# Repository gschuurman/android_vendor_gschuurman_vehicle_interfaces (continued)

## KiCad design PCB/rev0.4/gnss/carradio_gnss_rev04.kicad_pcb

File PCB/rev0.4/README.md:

# PCB rev 0.4: main board plus three plug-in modules

Rev 0.4 splits rev 0.3 into four boards so each one fits the JLCPCB 100 x 100 mm price tier, and spreads
the parts out for hand soldering (at least 0.8 mm between courtyards on every board).

| Board | Folder | Size | Layers | Holds |
|---|---|---|---|---|
| Main | `main/` | 100 x 100 mm, four M3 holes 4.5 mm in from each corner | 4 | RP2350B, TPS55288 VIM3/screen supply, always-on buck, car inputs, GNSS 3.3 V LDO, hub 1, HDMI-to-FPC screen adapter, loom connectors |
| GNSS module | `gnss/` | 26.5 x 31.5 mm | 2 | u-blox NEO-M9N, U.FL antenna receptacle with active-antenna feed, USB series resistors |
| Audio module | `audio/` | 36.5 x 41 mm | 2 | 2x PCM5102A, 2 LDOs, output filters |
| USB module | `usb/` | 36 x 55 mm (USB-A shells stick out 0.55 mm on the right) | 2 | Hub 2, two phone ports (LMR33630 5V/3A, TPS2561 limits, ESD), RTL-SDR USB-A socket |

Each board has its own schematic, PCB, PDF, netlist and BOM. **Status 2026-10-02: the three modules are routed (DRC clean); the main board is placed with the HDMI and TPS55288 copper in place, and its signal routing is still in progress.** All four come from `gen4.py` (`python3 gen4.py main|gnss|audio|usb`).

## Changes since the first rev 0.4 draft

- The NEO-M9N moved from the main board onto its own swappable GNSS module (Glenn, 2026-10-02). The antenna plugs into a
  U.FL receptacle J11 (Hirose U.FL-R-SMT-1, LCSC C88374); use a U.FL-to-SMA bulkhead pigtail to reach the car antenna.
- The GNSS module gets both USB and UART:
  - USB goes to hub 1 port 3 (it shows up as a CDC-ACM serial port, `/dev/ttyACM*`).
  - UART TX goes to the VIM3 UART_C RX (header pin 15) through R100 and to the RP2350B.
  - UART RX is driven by the VIM3 UART_C TX (header pin 16, through R101) or by the RP2350B, picked with
    solder jumper JP2: 1-2 VIM3 (default, bridged), 2-3 MCU. Cut the 1-2 trace and bridge 2-3 to hand GNSS
    config to the MCU.
- The RTL-SDR socket moved from hub 1 to hub 2 on the USB module, so USB module header pins 9 and 11 are now unused.
- J18 (VIM3 power, JST-XH) and J5 (power-on lead) now sit right below the VIM3 40-pin header at the top left.
- Parts now sit under the modules (MCU, hub 1, GNSS LDO, J21/J10), which freed space for wider spacing.
- Hub 1 (U13) now runs from the always-on +5V_AON instead of +5V_SYS, with a 10k pull-up (R104) on its reset pin.
  A blank RP2350B therefore enumerates as soon as 12V is applied, so the first flash works over USB (Glenn, 2026-10-02).

## How the modules stack

- The main board carries female sockets (8.5 mm tall): J27 (2x8) for GNSS, J23 (2x10) for audio, J25 (2x10) for USB.
- Each module has a male header (J28, J24, J26) **soldered on its underside**, pins pointing down. In KiCad the
  header footprint sits on the bottom layer, so pin n of the header lands on pin n of the socket.
- Each module PCB sits about 11 mm above the main board. Everything under a module is a low SMD part.
- One M2.5 standoff (11 mm) per module, at the far side from its header. Main-board positions:

| Module | Covers main board (x, y in mm) | Standoff hole on main |
|---|---|---|
| GNSS | 0-26.5, 19-50.5 | (3.2, 34.3) |
| Audio (turned 90°) | 27-63.5, 13-54 | (31.0, 16.5) |
| USB | 64-100, 32.5-87.5 (USB-A sockets on the right edge) | (67.8, 83.7) |

- J21 and J10 (main board headers) are under the USB module: unplug the module to reach them.
- SW1, SW2, JP1, Q2 and Q3 sit in the open strip between the audio and USB modules.

## Header pin maps

GNSS (J27 on main, J28 on module):

| Pin | Net | Pin | Net |
|---|---|---|---|
| 1 | +3V3_GNSS (switched by the MCU) | 2 | +3V3_GNSS |
| 3 | GND | 4 | +3V3_MCU (NEO V_BCKP, keeps hot start) |
| 5 | not connected | 6 | GND |
| 7 | GNSS_USB_DP | 8 | GNSS_TXD |
| 9 | GNSS_USB_DM | 10 | GNSS_RXD |
| 11 | GND | 12 | GND |
| 13 | GNSS_RST | 14 | GNSS_PPS |
| 15 | GNSS_SAFEBOOT | 16 | GND |

Audio (J23 on main, J24 on module):

| Pin | Net | Pin | Net |
|---|---|---|---|
| 1 | VIM3_5V | 2 | VIM3_5V |
| 3 | GND | 4 | GND |
| 5 | I2S_BCLK | 6 | GND |
| 7 | I2S_LRCK | 8 | VIM3_I2S_MCLK (spare) |
| 9 | I2S_DOUT0 | 10 | I2S_DOUT1 |
| 11 | VIM3_I2S_DOUT2 (spare) | 12 | DAC_XSMT |
| 13 | LUX_SCL (spare) | 14 | LUX_SDA (spare) |
| 15 | GND | 16 | GND |
| 17 | LINE_FL | 18 | LINE_FR |
| 19 | LINE_RL | 20 | LINE_RR |

USB (J25 on main, J26 on module):

| Pin | Net | Pin | Net |
|---|---|---|---|
| 1 | VSYS_IN (12V, for the 5V/3A buck) | 2 | VSYS_IN |
| 3 | GND | 4 | GND |
| 5 | +5V_SYS | 6 | +5V_SYS |
| 7 | GND | 8 | GND |
| 9 | not connected (was SDR) | 10 | HUB2_UP_DP |
| 11 | not connected (was SDR) | 12 | HUB2_UP_DM |
| 13 | GND | 14 | GND |
| 15 | MCU_USBP_PG | 16 | VIM3_PWR_EN |
| 17 | MCU_USBP_FAULT2 | 18 | MCU_USBP_FAULT1 |
| 19 | not connected | 20 | GND |

## GNSS in Android: what "native" needs

Today the project's GNSS HAL (`usb_gnss_hal/`, AIDL IGnss) reads NMEA from a hard-coded `/dev/ttyAML6` at 9600 baud
and sends UBX config itself. Android has no stock NMEA/serial GNSS HAL (AOSP's default one is a mock), so a HAL
of our own stays in the picture either way. "Native" here means letting the Linux kernel own the device.

UART path (kernel GNSS subsystem, `/dev/gnss0`):
1. Kernel config (vim3 fragment): `CONFIG_GNSS_SERIAL=m` and `CONFIG_GNSS_UBX_SERIAL=m` (`CONFIG_GNSS=m` is already on).
2. Device tree: a child node under `&uart_C`:
   `gnss { compatible = "u-blox,neo-m8"; current-speed = <38400>; };`
   The ubx driver has no M9 entry, but the neo-m8 binding works the same for the M9N. The driver also
   handles the `vcc`/`v-bckp` supplies if they are described; here the MCU switches the supply, so they can be left out.
3. HAL: open `/dev/gnss0` instead of `/dev/ttyAML6`, plus ueventd and sepolicy rules for `/dev/gnss*`.
   This also removes the clash between the `ttyAML.*` gnss label and the serial console.
4. Baud: the NEO-M9N UART default is 38400 (from memory; check the M9N integration manual), while the HAL uses 9600.

USB path (kept for the existing HAL design):
1. The NEO-M9N enumerates as u-blox VID 0x1546, CDC-ACM; `cdc-acm.ko` is already loaded, so it appears as `/dev/ttyACM*`.
2. Add a ueventd rule and a udev-style stable symlink by VID (or have the HAL scan `/sys/class/tty/ttyACM*` for VID 1546),
   plus sepolicy for that device.

Both paths can run at the same time; NEO-M9N outputs the same NMEA on UART and USB.

## RP2350B GPIO map (rev 0.4)

Re-assigned on 2026-10-02 so each signal leaves the QFN on the side facing its destination, which makes routing
possible. This replaces the rev 0.3 map in DESIGN_rev03.md; the draft firmware's pin table needs the same update.
Expansion nets are named after their GPIO (EXP_GPn).

| GPIO | Net | Notes |
|---|---|---|
| GPIO0 | MCU_BL_EN |  |
| GPIO1 | MCU_BL_PWM |  |
| GPIO2 | MCU_HUB_RST |  |
| GPIO3 | MCU_GNSS_PPS |  |
| GPIO4 | MCU_GNSS_TX | UART1 TX to GNSS (via JP2 2-3) |
| GPIO5 | MCU_GNSS_RX | UART1 RX from GNSS |
| GPIO6 | MCU_SBC_SENSE |  |
| GPIO7 | MCU_GNSS_RST |  |
| GPIO8 | MCU_GNSS_SAFEBOOT |  |
| GPIO9 | MCU_GNSS_EN |  |
| GPIO10 | MCU_DAC_MUTE |  |
| GPIO11 | EXP_GP11 | expansion header J10/J21 |
| GPIO12 | EXP_GP12 | expansion header J10/J21 |
| GPIO13 | EXP_GP13 | expansion header J10/J21 |
| GPIO14 | MCU_PARK_IN |  |
| GPIO15 | MCU_PWR_KEY |  |
| GPIO16 | MCU_BTN_MUTE |  |
| GPIO17 | MCU_BTN_VOLUP |  |
| GPIO18 | MCU_BTN_SCREEN |  |
| GPIO19 | MCU_SERVICE |  |
| GPIO20 | MCU_AMP_EN |  |
| GPIO21 | MCU_LED |  |
| GPIO22 | MCU_BTN_VOLDN |  |
| GPIO23 | MCU_VIM3_PWR_EN |  |
| GPIO24 | EXP_GP24 | expansion header J10/J21 |
| GPIO25 | EXP_GP25 | expansion header J10/J21 |
| GPIO26 | EXP_GP26 | expansion header J10/J21 |
| GPIO27 | EXP_GP27 | expansion header J10/J21 |
| GPIO28 | EXP_GP28 | expansion header J10/J21 |
| GPIO29 | EXP_GP29 | expansion header J10/J21 |
| GPIO30 | LUX_SDA | I2C1 SDA (light sensor, TPS55288, audio module) |
| GPIO31 | LUX_SCL | I2C1 SCL |
| GPIO32 | EXP_GP32 | J10 pin 2 (K-line UART TX) |
| GPIO33 | EXP_GP33 | J10 pin 3 (K-line UART RX) |
| GPIO34 | EXP_GP34 | expansion header J10/J21 |
| GPIO35 | MCU_REV_IN |  |
| GPIO36 | MCU_USBP_PG |  |
| GPIO37 | MCU_ILLUM_IN |  |
| GPIO38 | MCU_USBP_FAULT2 |  |
| GPIO39 | MCU_USBP_FAULT1 |  |
| GPIO40 | MCU_VBAT_ADC | ADC0 battery voltage |
| GPIO41 | MCU_5VSYS_ADC | ADC1 5V rail |
| GPIO42 | MCU_TEMP_ADC | ADC2 board temperature |
| GPIO43 | MCU_ACC_IN |  |
| GPIO44 | unused |  |
| GPIO45 | unused |  |
| GPIO46 | unused |  |
| GPIO47 | unused |  |

## Flashing the RP2350B

- Over USB: hold SW1 (BOOTSEL), tap SW2 (RESET); the chip shows up as a USB drive `RP2350` on whatever hosts hub 1.
  A blank flash starts the bootloader by itself. The host is normally the VIM3 (`picotool` from a root adb shell), or a PC
  on a breakout cable to J2 pins 2-5 (5V, D-, D+, GND) with the board off the VIM3 and 12V applied.
- Over SWD: J22 (SWCLK, GND, SWDIO, RUN) with a Raspberry Pi Debug Probe or a Pico running `debugprobe`, for recovery and debugging.
- Firmware should hold hub 1 in reset (MCU_HUB_RST low) while the VIM3 is off, to save parked current and keep the hub's
  D+ pull-up off the unpowered VIM3.

## Hand soldering

Most parts are 0805 or larger SOIC/SOT parts. These need hot air or a hotplate with paste, not an iron:
- RP2350B (QFN-80, 0.4 mm pitch), TPS55288 (VQFN-HR), NEO-M9N (LGA), Q11/Q12 and U16 (VSON/QFN power packages).
- J13 (HDMI) and J14 (0.5 mm FPC) have fine-pitch SMD pins; drag soldering with flux works, but check for bridges.
Ordering the bare boards with only those parts assembled by JLCPCB is an option.

## Main board notes

- HDMI J13 (top edge) to the screen FPC J14 (right edge) is routed on F.Cu over the In1 ground plane with no vias.
  Each pair is matched to 0.001 mm. An In1 rule area keeps vias out from under the runs.
- J14 keeps pin 1 on the right when seen from the top with the ribbon leaving the board edge.
- The TPS55288 power stage (U12, Q11/Q12, L3, gate resistors, snubber, net ties) is carried over from rev 0.3
  with its copper. +5V_SYS reaches J18 through an In2 copper strip.

## GNSS module notes

- The U.FL receptacle J11 sits at the module's left side, about 3 mm from the main board's left edge, so a pigtail can leave sideways.
- The RF line from J11 to the NEO is a 1.0 mm trace over solid B.Cu ground with stitching vias; B.Cu under it has
  no tracks. Check the 50 Ω width with the JLCPCB impedance calculator for the 2-layer 1.6 mm stack before ordering.
- L2 (active-antenna feed choke) is 0402, the one tiny passive left.

## Open items before ordering

- LCSC numbers for the 2x8 socket J27 and 2x8 header J28 (any 2.54 mm, 8.5 mm female socket fits).
- J23/J25 socket part C30867 was out of stock at LCSC on 2026-10-01; any 2x10 2.54 mm 8.5 mm female socket fits.
- The USB module's LMR33630 buck layout is auto-routed with widened copper; not yet checked against TI's layout guide.
- Bench test the TPS55288 loop (unchanged from rev 0.3).

## Layout scripts

`layout/` holds the scripts that made the boards (run in the `kicad/kicad:10.0` Docker image). See rev 0.3's
`layout/README.md` for the shared tools.

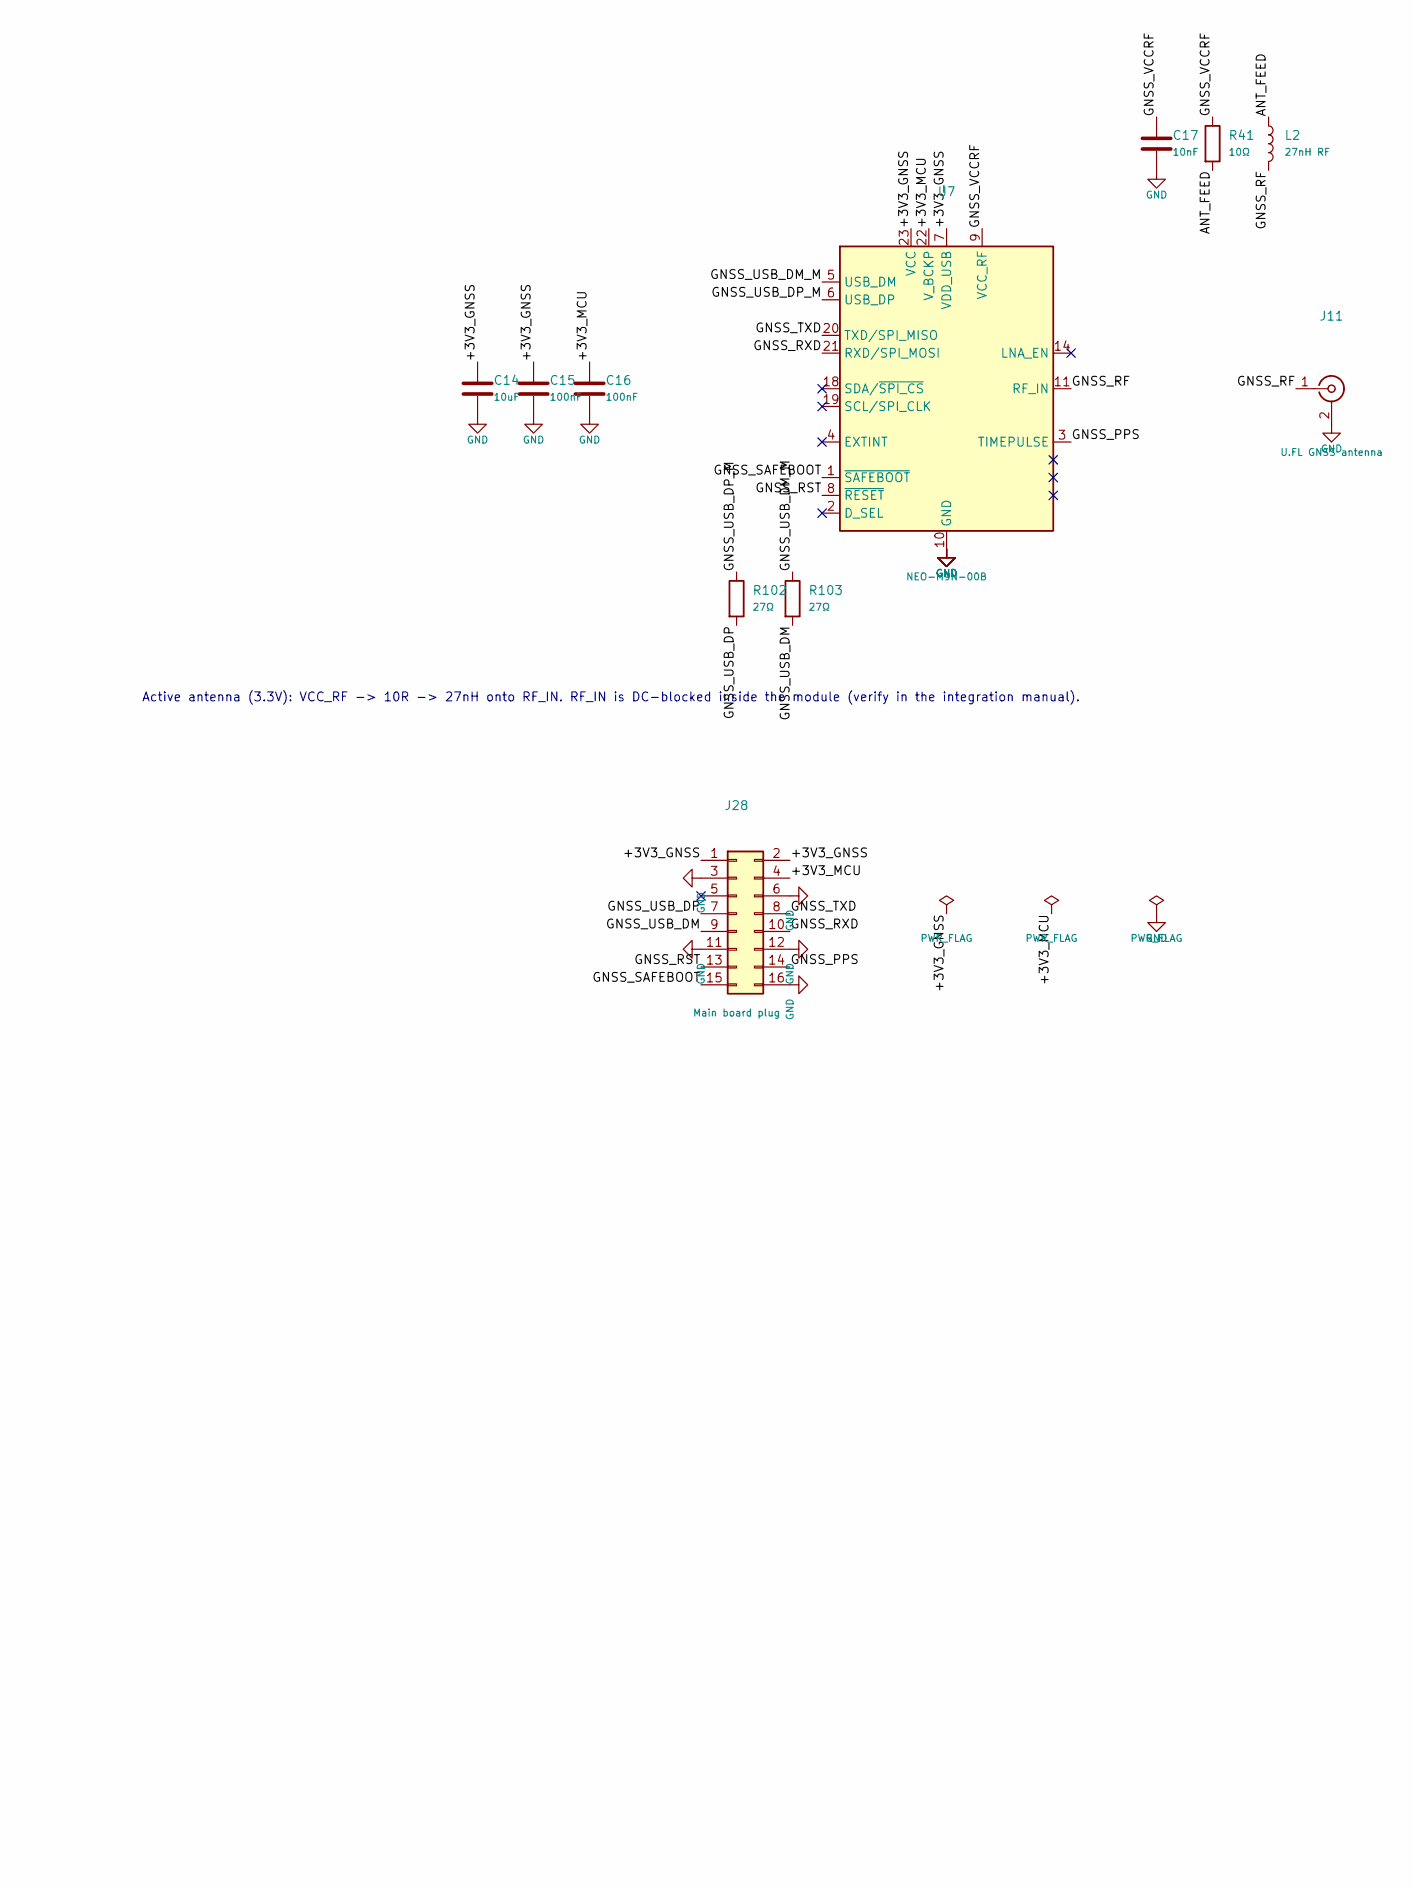
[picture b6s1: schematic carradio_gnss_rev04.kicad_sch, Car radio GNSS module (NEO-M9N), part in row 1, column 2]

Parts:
C14: 10uF; C_0805_2012Metric; MPN 0805 10uF 25V X5R; LCSC C15850
C15, C16: 100nF; C_0603_1608Metric; MPN 0603 100nF 50V X7R; LCSC C14663
C17: 10nF; C_0603_1608Metric; MPN 0603 10nF 50V X7R (Samsung CL10B103KB8N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; LCSC C1589
J11: U.FL GNSS antenna; U.FL_Hirose_U.FL-R-SMT-1_Vertical; MPN Hirose U.FL-R-SMT-1(80) U.FL receptacle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; LCSC C88374
J28: Main board plug; PinHeader_2x08_P2.54mm_Vertical; MPN 2x8 2.54mm male pin header
L2: 27nH RF; L_0402_1005Metric; MPN Murata LQG15HS27NJ02D; LCSC C12669
R41: 10Ω; R_0603_1608Metric; MPN 0603 10 1%; LCSC C22859
R102, R103: 27Ω; R_0603_1608Metric; MPN 0603 27 1%
U7: NEO-M9N-00B; ublox_NEO; MPN u-blox NEO-M9N-00B; LCSC C5119087

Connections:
/+3V3_GNSS: C14.1, C15.1, J28.1, J28.2, U7.7 (VDD_USB), U7.23 (VCC)
/+3V3_MCU: C16.1, J28.4, U7.22 (V_BCKP)
/ANT_FEED: L2.1, R41.2
/GNSS_PPS: J28.14, U7.3 (TIMEPULSE)
/GNSS_RF: J11.1 (In), L2.2, U7.11 (RF_IN)
/GNSS_RST: J28.13, U7.8 (~RESET)
/GNSS_RXD: J28.10, U7.21 (RXD/SPI_MOSI)
/GNSS_SAFEBOOT: J28.15, U7.1 (~SAFEBOOT)
/GNSS_TXD: J28.8, U7.20 (TXD/SPI_MISO)
/GNSS_USB_DM: J28.9, R103.2
/GNSS_USB_DM_M: R103.1, U7.5 (USB_DM)
/GNSS_USB_DP: J28.7, R102.2
/GNSS_USB_DP_M: R102.1, U7.6 (USB_DP)
/GNSS_VCCRF: C17.1, R41.1, U7.9 (VCC_RF)
GND: C14.2, C15.2, C16.2, C17.2, J11.2 (Ext), J28.3, J28.6, J28.11, J28.12, J28.16, U7.10 (GND), U7.12 (GND), U7.13 (GND), U7.24 (GND); also elsewhere on the board

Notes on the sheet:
Active antenna (3.3V): VCC_RF -> 10R -> 27nH onto RF_IN. RF_IN is DC-blocked inside the module (verify in the integration manual).
Car radio GNSS module rev 0.4 - NEO-M9N with SMA antenna jack; plugs onto the peripheral board (J28 -> J27). Generated by gen4.py gnss.

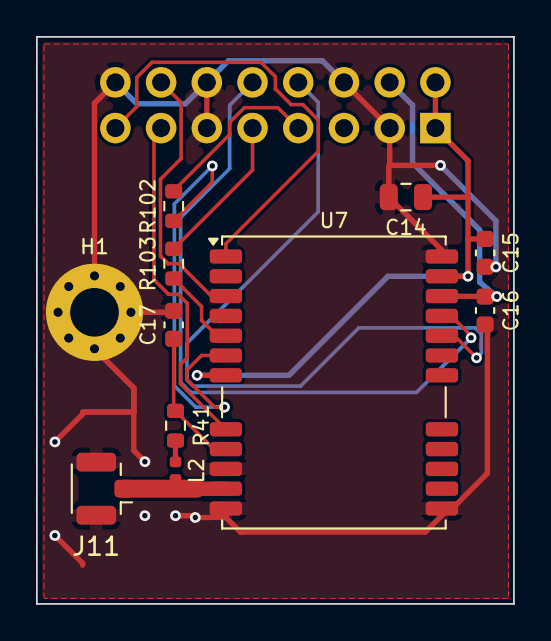
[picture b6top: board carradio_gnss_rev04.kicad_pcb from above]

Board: 2 copper layers, 26.5 x 31.5 mm, 12 parts (1 on the bottom side), 15 nets.

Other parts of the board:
H1: M2.5 standoff; MountingHole_2.7mm_M2.5_Pad_Via

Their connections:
GND: H1.1; also elsewhere on the board

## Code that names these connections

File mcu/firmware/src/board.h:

// RP2350B pin map for the car radio peripheral board, rev 0.6.
//
// Taken from the rev 0.6 main-board netlist (PCB/rev0.6/main/carradio_peripheral_rev06.net,
// U20). The comment after each pin names the net and the parts that set its idle level.
#pragma once

#define BOARD_REV 6

// ---- Car inputs: EL817 opto, emitter to the pin, 4.7k pull-down. High = 12V present. ----
#define PIN_ACC_IN        43  // /MCU_ACC_IN    U2, R4 (ISO A7, via F2)
#define PIN_ILLUM_IN      37  // /MCU_ILLUM_IN  U3, R6 (ISO A6)
#define PIN_REV_IN        35  // /MCU_REV_IN    U4, R30 (ISO A1)
#define PIN_PARK_IN       14  // /MCU_PARK_IN   U5, R32 (ISO A2, switch to ground; open = released)

// ---- Other inputs ----
#define PIN_SBC_SENSE      6  // /MCU_SBC_SENSE  VIM3 3.3V via R7 1k, R8 4.7k pull-down. High = VIM3 on
#define PIN_SERVICE       19  // /MCU_SERVICE    JP1 to 3.3V, R9 4.7k pull-down. High = service mode
#define PIN_USBP_PG       36  // /MCU_USBP_PG    USB module LMR33630 PG, R89 10k pull-up. High = good
#define PIN_USBP_FAULT1   39  // /MCU_USBP_FAULT1 TPS2561 FAULT, R87 10k pull-up. Low = over-current
#define PIN_USBP_FAULT2   38  // /MCU_USBP_FAULT2 R88 10k pull-up. Low = over-current
#define PIN_GNSS_PPS       3  // /MCU_GNSS_PPS   via R40 1k, R94 4.7k pull-down

// ---- Display buttons J12: switch to GND, 10k pull-up, 1k + 100nF RC. Low = pressed ----
#define PIN_BTN_SCREEN    18  // /MCU_BTN_SCREEN J12.1
#define PIN_BTN_VOLUP     17  // /MCU_BTN_VOLUP  J12.2
#define PIN_BTN_VOLDN     22  // /MCU_BTN_VOLDN  J12.3
#define PIN_BTN_MUTE      16  // /MCU_BTN_MUTE   J12.4

// ---- Outputs ----
#define PIN_VIM3_PWR_EN   23  // /MCU_VIM3_PWR_EN R73 1k -> TPS55288 EN + USB module enable; R72 100k pull-down
#define PIN_PWR_KEY       15  // /MCU_PWR_KEY    R12 390R -> AQY210S U22 LED. High = VIM3 power key pressed
#define PIN_AMP_EN        20  // /MCU_AMP_EN     R16 -> Q3 2N7002 -> amp remote (ISO A3). R15 pull-down
#define PIN_BL_EN          0  // /MCU_BL_EN      R23 -> panel FPC pin 37. R96 100k pull-down
#define PIN_BL_PWM         1  // /MCU_BL_PWM     R24 -> panel FPC pin 36. Inverted: low = brightest
#define PIN_DAC_MUTE      10  // /MCU_DAC_MUTE   R46 1k -> DAC XSMT, R47 10k pull-down. High = play
#define PIN_HUB_RST        2  // /MCU_HUB_RST    R90 1k -> CH334R RESET#, R104 10k pull-up. Drive low only
#define PIN_GNSS_EN        9  // /MCU_GNSS_EN    LP5907 U6 enable, R35 100k pull-down
#define PIN_GNSS_RST       7  // /MCU_GNSS_RST   R39 1k -> NEO RESET_N. Drive low only
#define PIN_GNSS_SAFEBOOT  8  // /MCU_GNSS_SAFEBOOT R79 1k -> NEO SAFEBOOT_N. Drive low only
#define PIN_LED           21  // /MCU_LED        R86 1k -> D16 green. High = on

// ---- UART1 to the GNSS (NEO-M9N UART1) ----
#define PIN_GNSS_TX        4  // /MCU_GNSS_TX    R37 -> GNSS RXD only when JP2 is set to 2-3
#define PIN_GNSS_RX        5  // /MCU_GNSS_RX    R38 from GNSS TXD, R95 4.7k pull-down
#define GNSS_UART          uart1

// ---- I2C1: BH1750 (J7), TPS55288 (U12), audio module, expansion J21. 4.7k pull-ups ----
#define PIN_I2C_SDA       30  // /LUX_SDA
#define PIN_I2C_SCL       31  // /LUX_SCL
#define BOARD_I2C          i2c1
#define TPS55288_ADDR     0x74  // MODE pin R67 = 0 ohm
#define BH1750_ADDR_L     0x23
#define BH1750_ADDR_H     0x5C

// ---- ADC (RP2350B: GPIO40..47 are ADC0..7) ----
#define PIN_VBAT_ADC      40  // ADC0 /MCU_VBAT_ADC  R10 1M / R11 220k from VBAT_P
#define PIN_5VSYS_ADC     41  // ADC1 /MCU_5VSYS_ADC R91 10k / R92 10k from +5V_SYS
#define PIN_TEMP_ADC      42  // ADC2 /MCU_TEMP_ADC  R93 10k to 3.3V, TH1 NTC 10k B3950 to GND
#define ADC_CH_VBAT        0
#define ADC_CH_5VSYS       1
#define ADC_CH_TEMP        2

// ---- K-line module socket J10 (not used by this firmware yet) ----
#define PIN_KLINE_TX      32  // /EXP_GP32 UART0 TX
#define PIN_KLINE_RX      33  // /EXP_GP33 UART0 RX
#define PIN_KLINE_EN      28  // /EXP_GP28

// Pins with nothing on them or only on expansion headers (J21: GPIO24..27).
// RP2350-E9: these are parked as inputs with the input buffer off and no pulls.
#define UNUSED_PINS {11, 12, 13, 24, 25, 26, 27, 28, 29, 32, 33, 34, 44, 45, 46, 47}

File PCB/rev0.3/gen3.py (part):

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cap("C11", "100n", 375, 109, "MCU_PARK_IN", "GND")
text("PARK (ISO A2, handbrake switch; may stay unwired)", 311, 83, 1.5)
cap("C8", "100n", 395, 60, "+3V3_MCU", "GND")
res("R57", "0", 545, 100, "AMP_REM", "ISO_A5", dnp=True, note="DNP: fit to also put the amp remote on ISO A5 (the usual antenna/amp remote pin)")
text("LED ~2.7mA at 14.4V; EL817 C-grade CTR >= 200%. 4.7k pull-downs satisfy RP2350-E9.", 215, 140)

# ================================================================ 3. amp remote
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res("R10", "1M", 146, 180, "VBAT_P", "MCU_VBAT_ADC", note="battery sense: 14.4V -> 2.6V")
res("R11", "220k", 154, 180, "MCU_VBAT_ADC", "GND")
cap("C9", "100n", 162, 180, "MCU_VBAT_ADC", "GND")
place(CG2, "JP1", "SERVICE jumper", 135, 215, {"1": "+3V3_MCU", "2": "MCU_SERVICE"}, "Connector_PinHeader_2.54mm:PinHeader_1x02_P2.54mm_Vertical", "", "1x2 2.54mm pin header + jumper")
res("R9", "4.7k", 150, 218, "MCU_SERVICE", "GND")
place(CG8, "J10", "Expansion", 185, 205, {"1": "+3V3_MCU", "2": "EXP_GP20", "3": "EXP_GP21", "4": "EXP_GP30", "5": "+5V_AON", "6": "GND", "7": "GND", "8": "EXP_GP31"},
      "Connector_PinHeader_2.54mm:PinHeader_1x08_P2.54mm_Vertical", "", "1x8 2.54mm pin header",
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       "3": "SDR_DM", "4": "SDR_DP", "1": "HUB2_UP_DM", "2": "HUB2_UP_DP"},
      "Package_SO:QSOP-16_3.9x4.9mm_P0.635mm", "C4154405", "WCH CH334R 4-port USB 2.0 hub, QSOP-16",
      note="pinout checked against WCH CH334 datasheet (CH334R column). Upstream = VIM3 header pins 3/4 (VIM3 hub port 4)")
place(add_lib('Device', 'Crystal_GND24'), "Y1", "12MHz", 660, 305, {"1": "HUB_XI", "3": "HUB_XO", "2": "GND", "4": "GND"}, "Crystal:Crystal_SMD_3225-4Pin_3.2x2.5mm", "",
      "12MHz crystal (pick in library)", note="CH334R has built-in load capacitors")
cap("C61", "1u", 720, 262, "+5V_SYS", "GND", note="at V5")
cap("C62", "10u", 728, 262, "HUB_3V3", "GND")
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       "10": "HUB2_UP_DM", "11": "HUB2_UP_DP", "7": "EXT1_DM", "8": "EXT1_DP", "5": "EXT2_DM", "6": "EXT2_DP", "3": None, "4": None, "1": None, "2": None},
      "Package_SO:QSOP-16_3.9x4.9mm_P0.635mm", "C4154405", "WCH CH334R 4-port USB 2.0 hub, QSOP-16",
      note="cascaded on hub 1 port 4. RESET#/CDP tied high = BC1.2 CDP for faster phone charging (WCH: depends on batch)")
place(add_lib('Device', 'Crystal_GND24'), "Y2", "12MHz", 530, 505, {"1": "HUB2_XI", "3": "HUB2_XO", "2": "GND", "4": "GND"}, "Crystal:Crystal_SMD_3225-4Pin_3.2x2.5mm", "", "12MHz crystal (pick in library)")
cap("C75", "1u", 580, 455, "+5V_SYS", "GND")
cap("C76", "10u", 588, 455, "HUB2_3V3", "GND")
cap("C77", "100n", 596, 455, "HUB2_3V3", "GND")
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               16: 16, 17: 17, 18: 18, 19: 19, 20: 20, 21: 21, 22: 22, 23: 23, 24: 25, 25: 26, 26: 27, 27: 28, 28: 36, 29: 37,
               30: 38, 31: 39, 32: 40, 33: 42, 34: 43, 35: 44, 36: 45, 37: 46, 38: 47, 39: 48,
               40: 49, 41: 52, 42: 53, 43: 54, 44: 55, 45: 56, 46: 57, 47: 58}
GPIO_NET = {0: "MCU_GNSS_TX", 1: "MCU_GNSS_RX", 2: "MCU_ACC_IN", 3: "MCU_REV_IN", 4: "LUX_SDA", 5: "LUX_SCL", 6: "MCU_ILLUM_IN",
            7: "MCU_PARK_IN", 8: "MCU_PWR_KEY", 9: "MCU_AMP_EN", 10: "MCU_BL_EN", 11: "MCU_BL_PWM", 12: "MCU_GNSS_EN",
            13: "MCU_SBC_SENSE", 14: "MCU_SERVICE", 15: "MCU_DAC_MUTE", 16: "MCU_BTN_SCREEN", 17: "MCU_BTN_VOLUP",
            18: "MCU_GNSS_RST", 19: "MCU_GNSS_PPS", 20: "EXP_GP20", 21: "EXP_GP21", 22: "MCU_BTN_VOLDN",
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for g, n in GPIO_NET.items(): rp_conns[str(RP_GPIO_PIN[g])] = n
for g in range(44, 48): rp_conns[str(RP_GPIO_PIN[g])] = None
place(RP, "U20", "RP2350B", 960, 150, rp_conns, "Package_DFN_QFN:QFN-80-1EP_10x10mm_P0.4mm_EP3.4x3.4mm", "", "Raspberry Pi RP2350B, QFN-80 (use the EasyEDA library footprint)",
      note="GPIO map in DESIGN_rev03.md. GPIO0-29 keep the rev 0.2 Pico numbers, except the battery ADC (GP26 -> GPIO40: only GPIO40-47 have ADC on the RP2350B)")

# 3.3V: low-quiescent LDO from the always-on 5.2V (the Pico module's own regulator is gone)
LDO33 = add_lib('Regulator_Linear', 'AP2112K-3.3')
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      note="place next to the TPS55288 / LMR33630: board temperature for thermal derating")
cap("C103", "100n", 916, 360, "MCU_TEMP_ADC", "GND")

# expansion: GPIO32-39
place(add_lib('Connector_Generic', 'Conn_01x10'), "J21", "Expansion 2", 1140, 200,
      {"1": "+3V3_MCU", "2": "EXP_GP32", "3": "EXP_GP33", "4": "EXP_GP34", "5": "EXP_GP35", "6": "EXP_GP36", "7": "EXP_GP37", "8": "EXP_GP38", "9": "EXP_GP39", "10": "GND"},
      "Connector_PinHeader_2.54mm:PinHeader_1x10_P2.54mm_Vertical", "", "1x10 2.54mm pin header", note="spare GPIO32-39 (e.g. CAN, extra UART/SPI)")
text("GPIO0-29 as rev 0.2 except: GPIO40 battery ADC (was GP26), GPIO23/24 USB port faults, GPIO25 LED, GPIO26 USB supply PG,", 860, 400)
text("GPIO29 GNSS safeboot, GPIO30/31 on J10, GPIO32-39 on J21, GPIO41 5V rail ADC, GPIO42 board temperature, GPIO43 hub 1 reset.", 860, 404)

# RP2350-E9 (input pad can latch near 2V with only the internal pull-down): every MCU input that can float
# gets an external resistor. Pull-downs are 4.7k (below the ~8.2k the erratum workaround calls for).
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
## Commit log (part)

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2025-11-20 Add a hal
2025-11-20 New Implementation
2025-11-20 Update vehicle_ndk to v3
2025-11-20 Fix import
2025-11-20 Implement missing methods
2025-11-20 First compiling HAL
2025-11-20 configure emulator
2025-11-20 Use system properties for device paths
2025-11-20 Refactor code for readability
2025-11-23 Update SDK Version
2025-11-25 add evs config
2025-11-25 Fix file conflict
2025-12-06 Update HAL
2025-12-06 rename evs
2025-12-06 Remove libgpiod
2025-12-06 No exceptions
2025-12-07 Fix paths
2025-12-08 Resolve pwm controller based on memory adress
2025-12-08 PWM fix:now working on boot, screen might still flicker on adjustment. Timing improvements required
2025-12-09 Add debouncing to kernel writes
    Make sure that we are not spamming the kernel when changing brightness,
    If the level is the same, dont write it to the sysfs endpoint
2025-12-09 Add bh1750 support
2025-12-09 Fix pwm init
2025-12-10 Optimize init sequence for slow kernel
2025-12-10 Fix pwm enable
2025-12-22 Add audio controll hal
2025-12-23 Fix build
2026-01-04 Add controll
2026-01-04 Add Balance and fader apps
2026-01-09 FeatureDump
2026-01-10 Update VHAL for gear polling
2026-01-12 Fix Pin Allocation
2026-01-13 Do not close file handle for gpio pin
2026-01-14 Fix reverse camera detection
2026-01-14 Add fallback if variable is undefined
2026-01-21 Test c++ rvc service
2026-01-26 Force VHAL to report parked
2026-01-30 Add gnss usb serial service
2026-02-15 enable scanning of AML serial devices
2026-02-19 Fixes for GPS and Lineage 23.2
2026-03-08 Add RRO for power button override
2026-05-03 Fix VHAL for gear selection
2026-05-06 Reboot wifi to fix co-existence
2026-05-10 Add AA RRO
2026-06-28 Add pi pico firmware for vim3 input controll
